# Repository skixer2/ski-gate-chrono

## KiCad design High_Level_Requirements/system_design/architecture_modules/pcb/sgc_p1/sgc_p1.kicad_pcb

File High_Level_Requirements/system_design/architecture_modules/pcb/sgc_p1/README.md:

# SGC P1 — KiCad 8 schematic (generated capture)

**Board:** SGC P1 standalone carrier for u-blox ANNA-B402 — 22 × 55 mm, 4-layer, 0.8 mm, ENIG.
**Source of truth:** `../../sgc_schematic_spec.md` v0.1 (commit 92b352e). Every pin number, pin name
and net in this capture is traceable to that spec (or the datasheet texts it cites). Nothing invented;
everything the spec marks TBD-JP appears as a **text note**, never as a guessed value/net.

## Files

| File | What |
|---|---|
| `sgc_p1.kicad_pro` | KiCad 8 project (minimal) |
| `sgc_p1.kicad_sym` | Project symbol library — 21 symbols (12 ICs/connectors + R/C/L/LED_RGB + 5 power symbols) |
| `sgc_p1.kicad_sch` | Single A3 landscape sheet, KiCad 8 format (version 20231120) |
| `sgc_netlist.py` | **Data**: symbol pin tables + per-component net assignment (edit here first) |
| `gen_symbols.py` | Regenerates `sgc_p1.kicad_sym` from the netlist |
| `gen_schematic.py` | Regenerates `sgc_p1.kicad_sch` + `sgc_p1.kicad_pro` |
| `validate_sgc_p1.py` | Mandatory validation (see below) |

## How to open (KiCad 8.x)

1. Open KiCad 8 → *File → Open Project* → select `sgc_p1.kicad_pro`.
2. Add the symbol library once: *Preferences → Manage Symbol Libraries → Project Libraries → add*
   → `sgc_p1.kicad_sym` (nickname `sgc_p1`). The schematic already embeds every used symbol in its
   `lib_symbols` section, so the sheet displays even before you register the library.
3. Open `sgc_p1.kicad_sch` in Eeschema.

**Regenerate after edits - THREE steps, in this order (order matters):**

```
python3 preserve_layout.py preserve   # 0. capture JP's manual symbol moves (ALWAYS first!)
python3 gen_symbols.py       # 1. regenerate sgc_p1.kicad_sym from SYMBOL_PINS
python3 gen_schematic.py     # 2. write root + child sheets; AUTO re-applies JP's placements
python3 validate_sgc_p1.py   # 3. mandatory validation (all sheets round-trip + union)

PCB stage (since 2026-11-27):

python3 gen_pcb.py          # 4. generate sgc_p1.kicad_pcb: 22x55 board, 79 parts placed per
                            #    PLACEMENT_PLAN v2 (placement_check.P), pads netted from netlist
python3 verify_pcb.py       # 5. semantic gate: re-reads the board file, transforms back to
                            #    plan space, enforces gaps/edges/keepouts on TRUE pad geometry

JP placement preservation (since 2026-11-27): JP moves symbols in KiCad and saves;
'preserve' harvests his positions into layout_positions.json (committed), and
gen_schematic.py translates each part + its labels/stubs/props accordingly.
Translation moves are fully preserved. Symbol ROTATION is not preserved yet
(warned at generation; validator catches label/pin mismatch).
```

**Structure (N1 7-page split, JP GO 2026-11-04):** "sgc_p1.kicad_sch" is a hierarchy-only
root (Arduino ABX00050 style) with six child sheets from "SHEETS" in "sgc_netlist.py":
sch_power (charger/gauge/battery) - sch_mcu (ANNA-B402 + Y1 + SWD) - sch_sensors (BHI260AP
cluster + RGB) - sch_storage (dual MX25R flash) - sch_boost_led (v2 DNP reserve) -
sch_connectors (USB-C/battery/piezo). Every ref sits on exactly ONE sheet (generator
asserts coverage); all connectivity is global labels + power symbols, so sheets bridge by
name with no hierarchical pins. Child-sheet uuids are deterministic (uuid5) so repeated
regeneration keeps the .kicad_pro sheet map stable.

Gotchas learned the hard way:
- kiutils is a hard dependency and does NOT survive a container restart:
  run "pip install --break-system-packages kiutils" (PEP-668 managed Python).
- A crash inside kiutils to_file() can TRUNCATE the target file before writing - if a
  generation run fails, expect zero-byte/partial outputs and re-run after fixing.
- The retired 2-sheet era lives in git history (split_led_sheet.py, led_reserve.kicad_sch);
  the text-surgery approach was dropped for data-driven multi-sheet generation.

Add `--break-system-packages` only because this is a PEP-668 managed Python.
(requires `pip install kiutils`). Edit `sgc_netlist.py`, not the generated files.

## Layout of the sheet (grouped by subsystem)

- **Top-left:** USB-C (J1), CC Rd resistors, VBUS bulk, BQ25120A charger + its R/C network.
- **Bottom-left:** MAX17048 gauge, JST-3 battery connector, SWD header (J3).
- **Center:** ANNA-B402 (U1, all 56 pins incl. 4/7/8 GND from Table 4) + antenna keepout note.
- **Right:** BHI260AP (U8, all 44 pads), BMP390L (U9), flash U7/U2, IS31FL3194 (U5) + RGB LED (D1).
- **Bottom-middle:** LDC1612 (U6, DNP v2) + peripheral/v2 notes (boost, SK6812, Y1, TPs, DNP list).

Connectivity style: **global labels on short stubs** for every pin (61 named nets) + **power symbols**
(`#PWR01…`, per zone anchors) on the power nets GND / +1V8 / VBAT / V_PMID / VBUS_USB. No sprawling wires.
Note boxes carry all OD callouts, the antenna keepout (SIM App. B), I²C address map and the peripheral/v2 notes.

## Refdes scheme (per task; spec's Nicla numbering preserved where it matters)

U1 ANNA-B402 · U2 MX25R1635F (BHI FW flash, OD-5) · U3 BQ25120A · U4 MAX17048 · U5 IS31FL3194 ·
U6 LDC1612 (DNP) · U7 MX25R6435F · U8 BHI260AP · U9 BMP390L · J1 USB4085 · J2 JST-3 battery ·
J3 SWD 2×5 · D1 SMLP34RGB2W3 · C1–C16 · R1–R10 · L1. (Nicla-schematic numbering had IS31=U8 — remapped here.)

## What is decided vs TBD-JP (OD summary — all also on the sheet as notes)

**Decided & captured:** charger resistor network (1.82k/1k/4.99k/100k), all decoupling per spec §6,
I²C pull-ups 100 k→+1V8 (i2c0), BHI RESETN→P0.13 (C3/OD-7), BQ CD→P0.08 + 100k PU V_PMID (C2/OD-8),
boost EN→P0.17 (C1), gauge ALRT→P0.21 + 10k PU, XL2→GND, ANT_INT↔ANT bridge, ANT_PCB→GND pattern
(corner placement), U2 QSPI nets, LDC ADDR→GND (0x2A) + INTB→BUTTON (OD-11), SWD pinout.

**TBD-JP — represented as notes only (never guessed):**
- **OD-4** battery connector PN + cell confirm; NTC R_HI/R_LO values (need Renata R25/B).
- **OD-5** U2 added to BOM (drawn populated, Nicla parity).
- **OD-6** BME688 populate-vs-DNP (not drawn; note at U8 — rides BHI M1 with BMM150).
- **OD-9 / OD-9b** +5 V level translator part (TXB0102-class); SK6812 strip stays on P0.19 pending R2 bench.
- **OD-10** Y1 SIT1532AI fit (default fit; XL1 net `32K_XL1`, note only).
- **OD-12** MAX17048 VIH vs 1.8 V pull-ups — verify before freezing pull-up rail.
- **OD-13** USB ESD part (PESD5V0U2UT vs TPD4E05U06) — note at J1, not drawn.
- **OD-16** module order code + corner placement confirm.
- **OD-17** IS31 SDB net on Nicla + its decap value (SDB→V_PMID drawn per default).
- BHI **HOSTBOOT(3)/VREG(6)** NC v1 (not in spec §6 — decoupling TBD-JP vs Bosch ds); M1/M2/M3 cluster
  wiring = **copy ABX00050 at capture** (BMM150/BME688 not drawn); BMP390 INT(7) NC (DNC per ds);
  RGB LED common polarity verify (IS31 OUTs are current sinks; spec text says anodes to OUTs).
- Boost (MT3608 + SK6812 ×5), RV-3028-C7, U2/strip passives: **note boxes only** — capture at layout. *(BZ1 beeper removed from the project 2026-11-22 — F14, no footprint.)*
- TP set per OD-3: note only.

## Footprint guidance

Pre-assigned (standard lib): R/C/L 0402 (caps ≥4.7 µF 0603), U7/U2 `Package_SO:SOIC-8_5.23x5.23mm_P1.27mm`.
Left EMPTY → **custom footprints needed:** U1 ANNA-B402 LGA pattern (u-blox land pattern), U3 BQ25120A
YFP-25 DSBGA, U4 MAX17048 TDFN-8, U8 BHI260AP LGA-44, U5 IS31 WLCSP-8, U9 BMP390 LGA-10, U6 LDC WSON-12,
J1 USB4085 mid-mount, J2 JST-3 (PN per OD-4), J3 (2×5 1.27 mm Cortex-Debug style **or Tag-Connect
TC2050** per OD-2), D1 SMLP34RGB2W3. These can be generated later from the datasheet land patterns.

## Console pads + pogo jig (rev A)

`TP_TX` (P0.20) / `TP_RX` (P0.09) / `TP_GND` are bare 1.0 mm ENIG test points for a
bidirectional UART console. They carry no part, no BOM line, no assembly step and no
current, so they stay on production units at zero cost (JP 2026-11-22).

**Registration:** `MH1`/`MH2` are 1.6 mm NPTH holes and `FID1`/`FID2` are optical
fiducials, so a printed jig can be located. The hole pair is **deliberately asymmetric**
(17 mm / 13 mm either side of the pad centroid): a symmetric pair lets the jig drop on
180 degrees rotated, which would land jig-TX on TP_GND and jig-GND on TP_TX - two outputs
driving each other with no current limiting.

**PROVISIONAL:** there is no PCB layout yet, so the coordinates in `sgc_netlist.py` are
schematic-sheet millimetres, not board positions. Treat MH/FID and the 10 mm pad pitch as
intent, not fab data. Final pad/hole datum must be set in layout against the printed jig
(JP designs and prints the jig). Pad pitch is shown at 10 mm for schematic legibility and
can be tightened once wire routing is regenerated for the new positions.

**Do NOT use magnetic-base probe fixtures** (e.g. PCBite) on this board: the BMM150 is
populated and its magnetometer feeds the BHY260AP rotation-vector fusion, so nearby
permanent magnets corrupt heading and calibration.

## ERC / validation status

- **Syntax:** both KiCad files parse clean with kiutils (round-trip write + re-read) — see below.
- **Netlist:** independently re-extracted from sheet geometry (wire endpoints + labels + power symbols)
  and compared pin-by-pin against `sgc_netlist.py`: **271/271 pin connections correct, 0 shorts,
  0 floating labels, 0 mid-span taps** (the hidden-short class KiCad auto-junctions).
- **Census:** 40 components (9 U + 3 J + 16 C + 10 R + 1 L + 1 D) vs spec net lists; pin counts:
  B402 56, BQ 25, MAX17048 9 (incl. EP), BHI 44, BMP390 10, LDC 12, IS31 8, MX25R 8+8, USB4085 20, JST 3, SWD 10.
- **NOT claimed:** no electrical-correctness/ERC guarantee beyond the above — run KiCad's ERC after JP
  review; expect informational warnings (single-sheet, NC pins on unused pads, v2 reserved nets).

Run validation: `python3 validate_sgc_p1.py` (exit 0 = green).

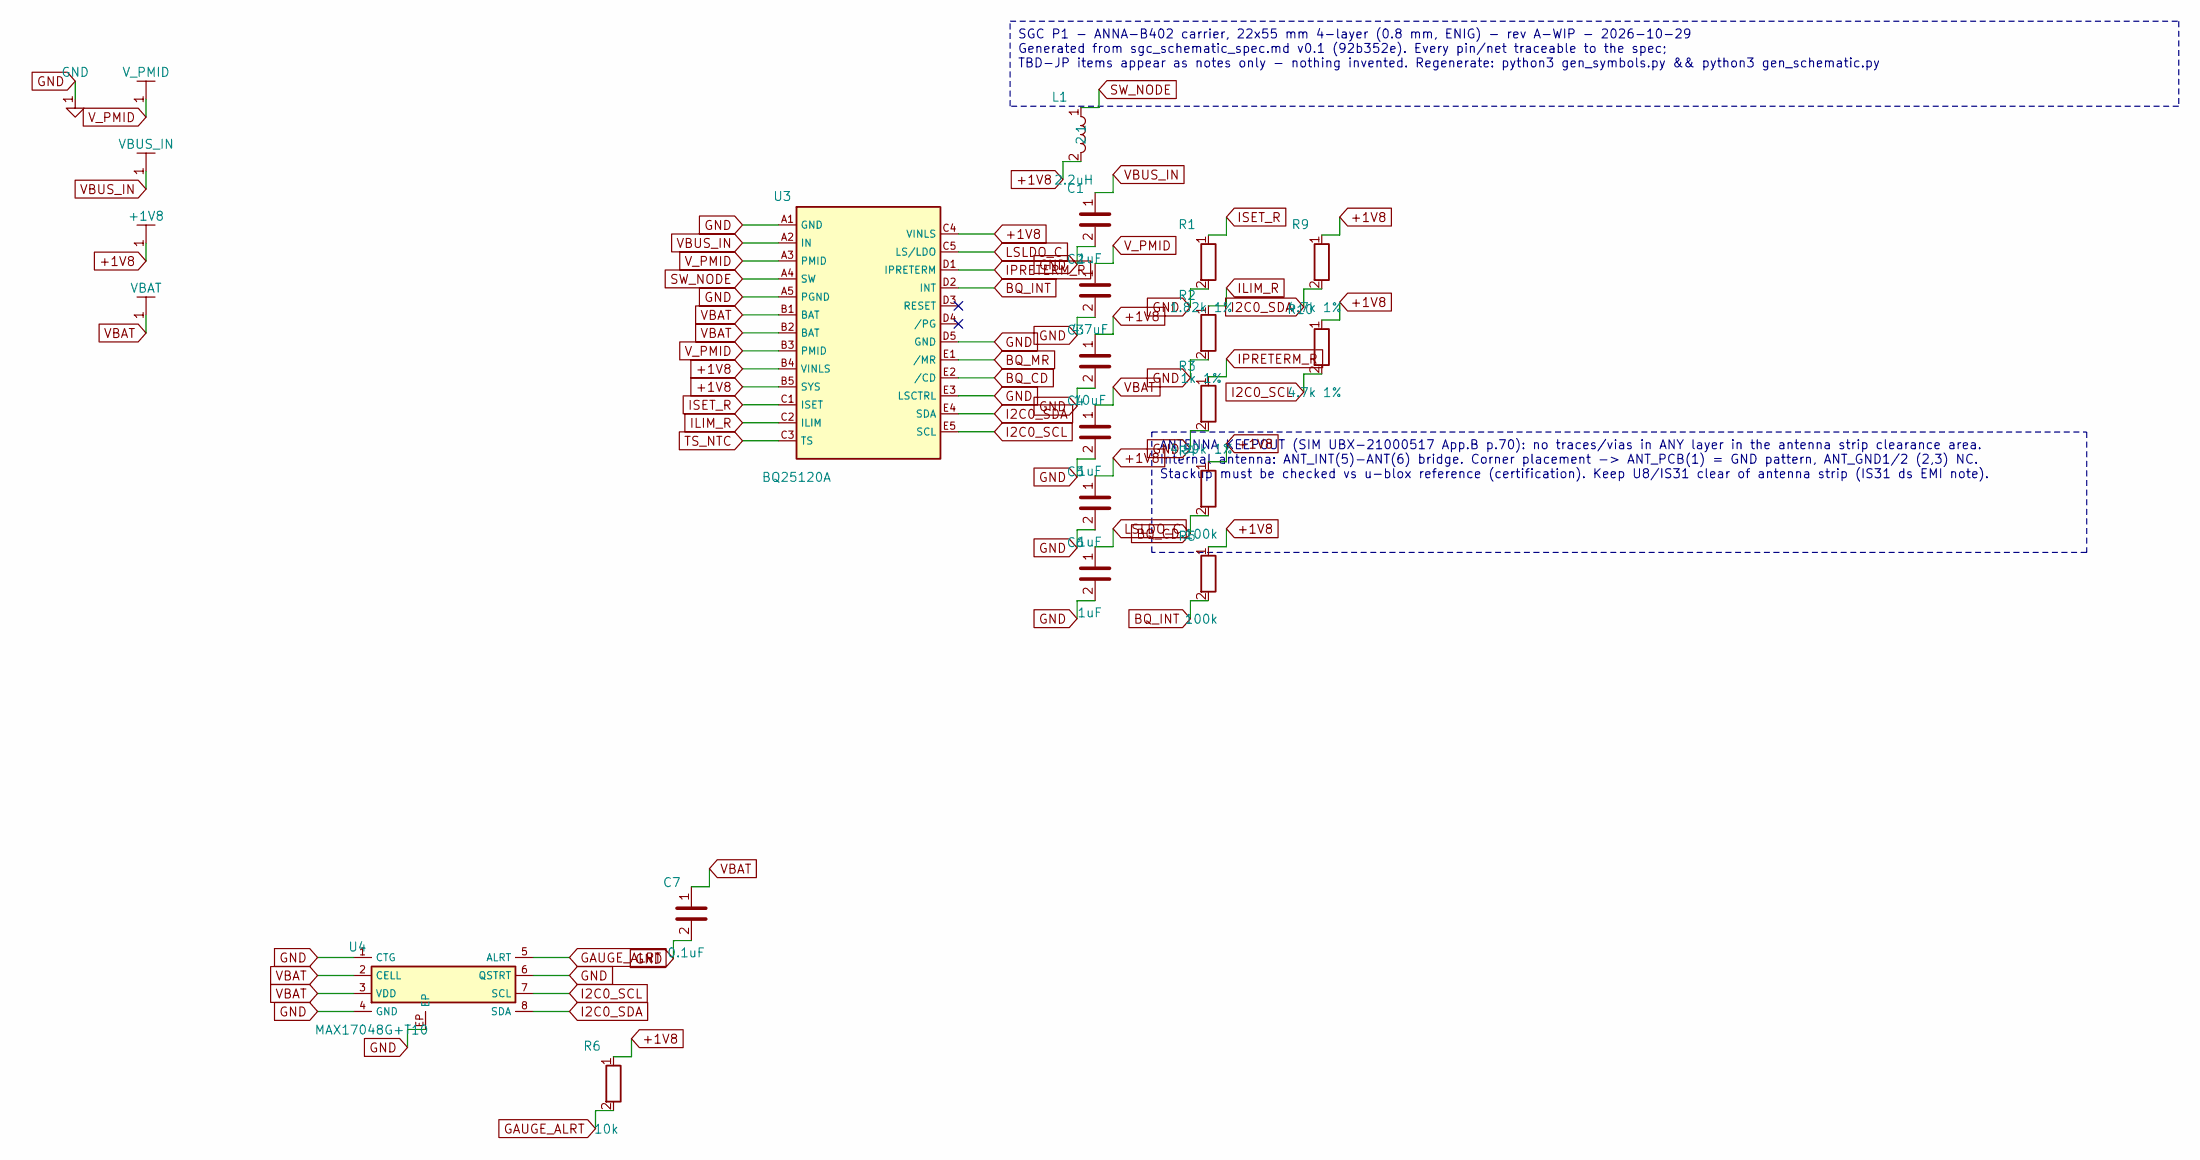
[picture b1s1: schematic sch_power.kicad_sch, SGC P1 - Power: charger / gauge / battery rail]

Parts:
C1, C4, C5, C6: 1uF; C_0402_1005Metric
C2: 4.7uF; C_0603_1608Metric
C3: 10uF; C_0603_1608Metric
C7: 0.1uF; C_0402_1005Metric
L1: 2.2uH; L_0603_1608Metric
R1: 1.82k 1%; R_0402_1005Metric
R2: 1k 1%; R_0402_1005Metric
R3: 4.99k 1%; R_0402_1005Metric
R4, R5: 100k; R_0402_1005Metric
R6: 10k; R_0402_1005Metric
R9, R10: 4.7k 1%; R_0402_1005Metric
U3: BQ25120A; Texas_DSBGA-25_YFP0025_1.6x1.6mm_Layout5x5_P0.4mm
U4: MAX17048G+T10; Maxim_TDFN-8-1EP_2x2mm_P0.5mm_EP0.8x1.38mm_MAX17048

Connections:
+1V8: C3.1, C5.1, L1.2, R4.1, R5.1, R6.1, R9.1, R10.1, U3.B4 (VINLS), U3.B5 (SYS), U3.C4 (VINLS); also elsewhere on the board
BQ_CD: R4.2, U3.E2 (/CD); also elsewhere on the board
BQ_INT: R5.2, U3.D2 (INT)
BQ_MR: U3.E1 (/MR); also elsewhere on the board
GAUGE_ALRT: R6.2, U4.5 (ALRT); also elsewhere on the board
GND: C1.2, C2.2, C3.2, C4.2, C5.2, C6.2, C7.2, R1.2, R2.2, R3.2, U3.A1 (GND), U3.A5 (PGND), U3.D5 (GND), U3.E3 (LSCTRL), U4.1 (CTG), U4.4 (GND), U4.6 (QSTRT), U4.EP; also elsewhere on the board
I2C0_SCL: R10.2, U3.E5 (SCL), U4.7 (SCL); also elsewhere on the board
I2C0_SDA: R9.2, U3.E4 (SDA), U4.8 (SDA); also elsewhere on the board
ILIM_R: R2.1, U3.C2 (ILIM)
IPRETERM_R: R3.1, U3.D1 (IPRETERM)
ISET_R: R1.1, U3.C1 (ISET)
LSLDO_C: C6.1, U3.C5 (LS/LDO)
SW_NODE: L1.1, U3.A4 (SW)
TS_NTC: U3.C3 (TS); also elsewhere on the board
VBAT: C4.1, C7.1, U3.B1 (BAT), U3.B2 (BAT), U4.2 (CELL), U4.3 (VDD); also elsewhere on the board
VBUS_IN: C1.1, U3.A2 (IN); also elsewhere on the board
V_PMID: C2.1, U3.A3 (PMID), U3.B3 (PMID); also elsewhere on the board

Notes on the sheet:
SGC P1 - ANNA-B402 carrier, 22x55 mm 4-layer (0.8 mm, ENIG) - rev A-WIP - 2026-10-29 Generated from sgc_schematic_spec.md v0.1 (92b352e). Every pin/net traceable to the spec; TBD-JP items appear as notes only - nothing invented. Regenerate: python3 gen_symbols.py && python3 gen_schematic.py
ANTENNA KEEPOUT (SIM UBX-21000517 App.B p.70): no traces/vias in ANY layer in the antenna strip clearance area. Internal antenna: ANT_INT(5)-ANT(6) bridge. Corner placement -> ANT_PCB(1) = GND pattern, ANT_GND1/2 (2,3) NC. Stackup must be checked vs u-blox reference (certification). Keep U8/IS31 cl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

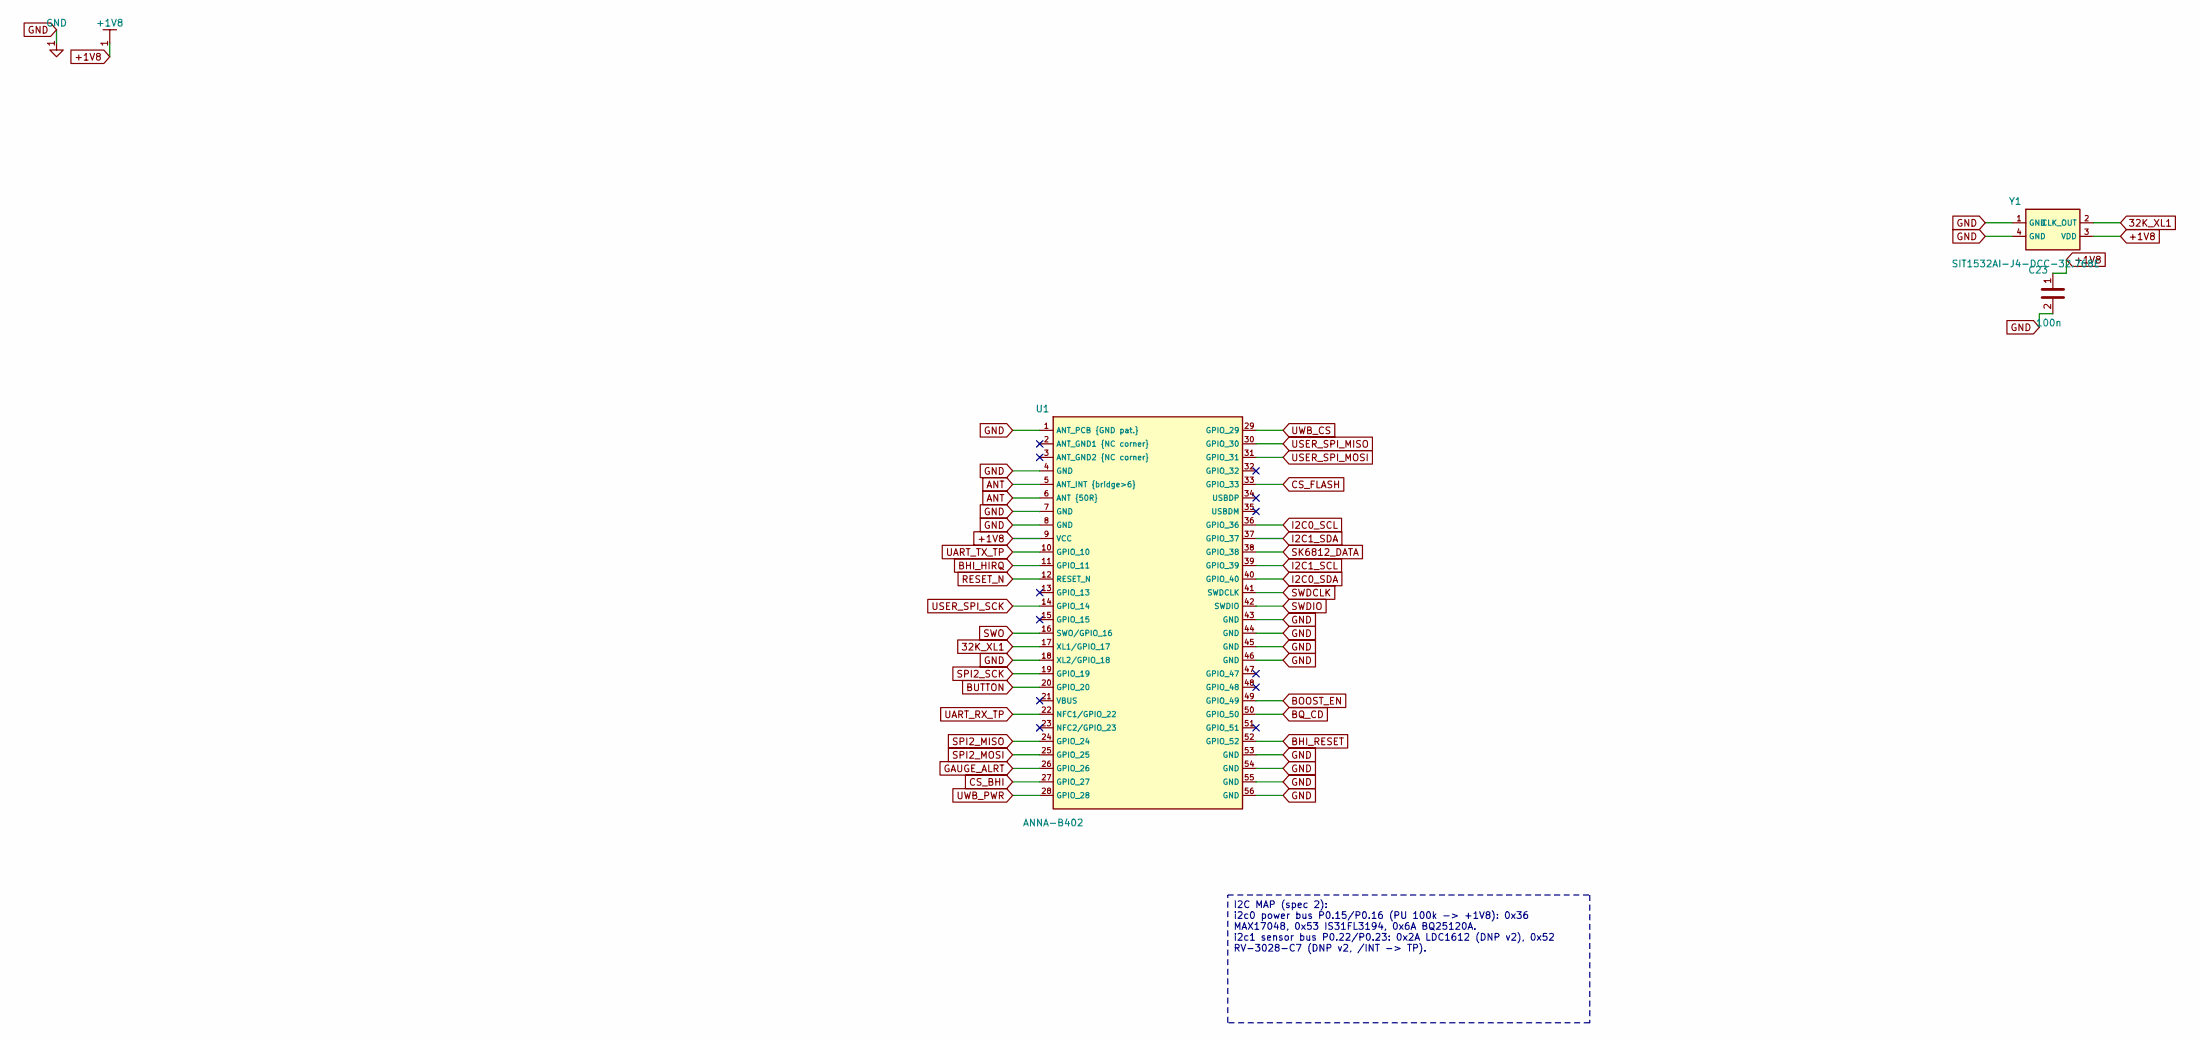
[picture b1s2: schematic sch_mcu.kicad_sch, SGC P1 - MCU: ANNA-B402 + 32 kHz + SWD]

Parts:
C23: 100n; C_0402_1005Metric
U1: ANNA-B402; ANNA-B402_UBL
Y1: SIT1532AI-J4-DCC-32.768E; SIT1532_CSP-4_1p5x0p8mm

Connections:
32K_XL1: U1.17 (XL1/GPIO_17), Y1.2 (CLK_OUT)
+1V8: C23.1, U1.9 (VCC), Y1.3 (VDD); also elsewhere on the board
ANT: U1.5 (ANT_INT {bridge>6}), U1.6 (ANT {50R})
BHI_HIRQ: U1.11 (GPIO_11); also elsewhere on the board
BHI_RESET: U1.52 (GPIO_52); also elsewhere on the board
BOOST_EN: U1.49 (GPIO_49); also elsewhere on the board
BQ_CD: U1.50 (GPIO_50); also elsewhere on the board
BUTTON: U1.20 (GPIO_20); also elsewhere on the board
CS_BHI: U1.27 (GPIO_27); also elsewhere on the board
CS_FLASH: U1.33 (GPIO_33); also elsewhere on the board
GAUGE_ALRT: U1.26 (GPIO_26); also elsewhere on the board
GND: C23.2, U1.1 (ANT_PCB {GND pat.}), U1.4 (GND), U1.7 (GND), U1.8 (GND), U1.18 (XL2/GPIO_18), U1.43 (GND), U1.44 (GND), U1.45 (GND), U1.46 (GND), U1.53 (GND), U1.54 (GND), U1.55 (GND), U1.56 (GND), Y1.1 (GND), Y1.4 (GND); also elsewhere on the board
I2C0_SCL: U1.36 (GPIO_36); also elsewhere on the board
I2C0_SDA: U1.40 (GPIO_40); also elsewhere on the board
I2C1_SCL: U1.39 (GPIO_39); also elsewhere on the board
I2C1_SDA: U1.37 (GPIO_37); also elsewhere on the board
RESET_N: U1.12 (RESET_N); also elsewhere on the board
SK6812_DATA: U1.38 (GPIO_38); also elsewhere on the board
SPI2_MISO: U1.24 (GPIO_24); also elsewhere on the board
SPI2_MOSI: U1.25 (GPIO_25); also elsewhere on the board
SPI2_SCK: U1.19 (GPIO_19); also elsewhere on the board
SWDCLK: U1.41 (SWDCLK); also elsewhere on the board
SWDIO: U1.42 (SWDIO); also elsewhere on the board
SWO: U1.16 (SWO/GPIO_16); also elsewhere on the board
UART_RX_TP: U1.22 (NFC1/GPIO_22); also elsewhere on the board
UART_TX_TP: U1.10 (GPIO_10); also elsewhere on the board
USER_SPI_MISO: U1.30 (GPIO_30)
USER_SPI_MOSI: U1.31 (GPIO_31)
USER_SPI_SCK: U1.14 (GPIO_14)
UWB_CS: U1.29 (GPIO_29)
UWB_PWR: U1.28 (GPIO_28)

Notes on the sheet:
I2C MAP (spec 2): i2c0 power bus P0.15/P0.16 (PU 100k -> +1V8): 0x36 MAX17048, 0x53 IS31FL3194, 0x6A BQ25120A. i2c1 sensor bus P0.22/P0.23: 0x2A LDC1612 (DNP v2), 0x52 RV-3028-C7 (DNP v2, /INT -> TP).

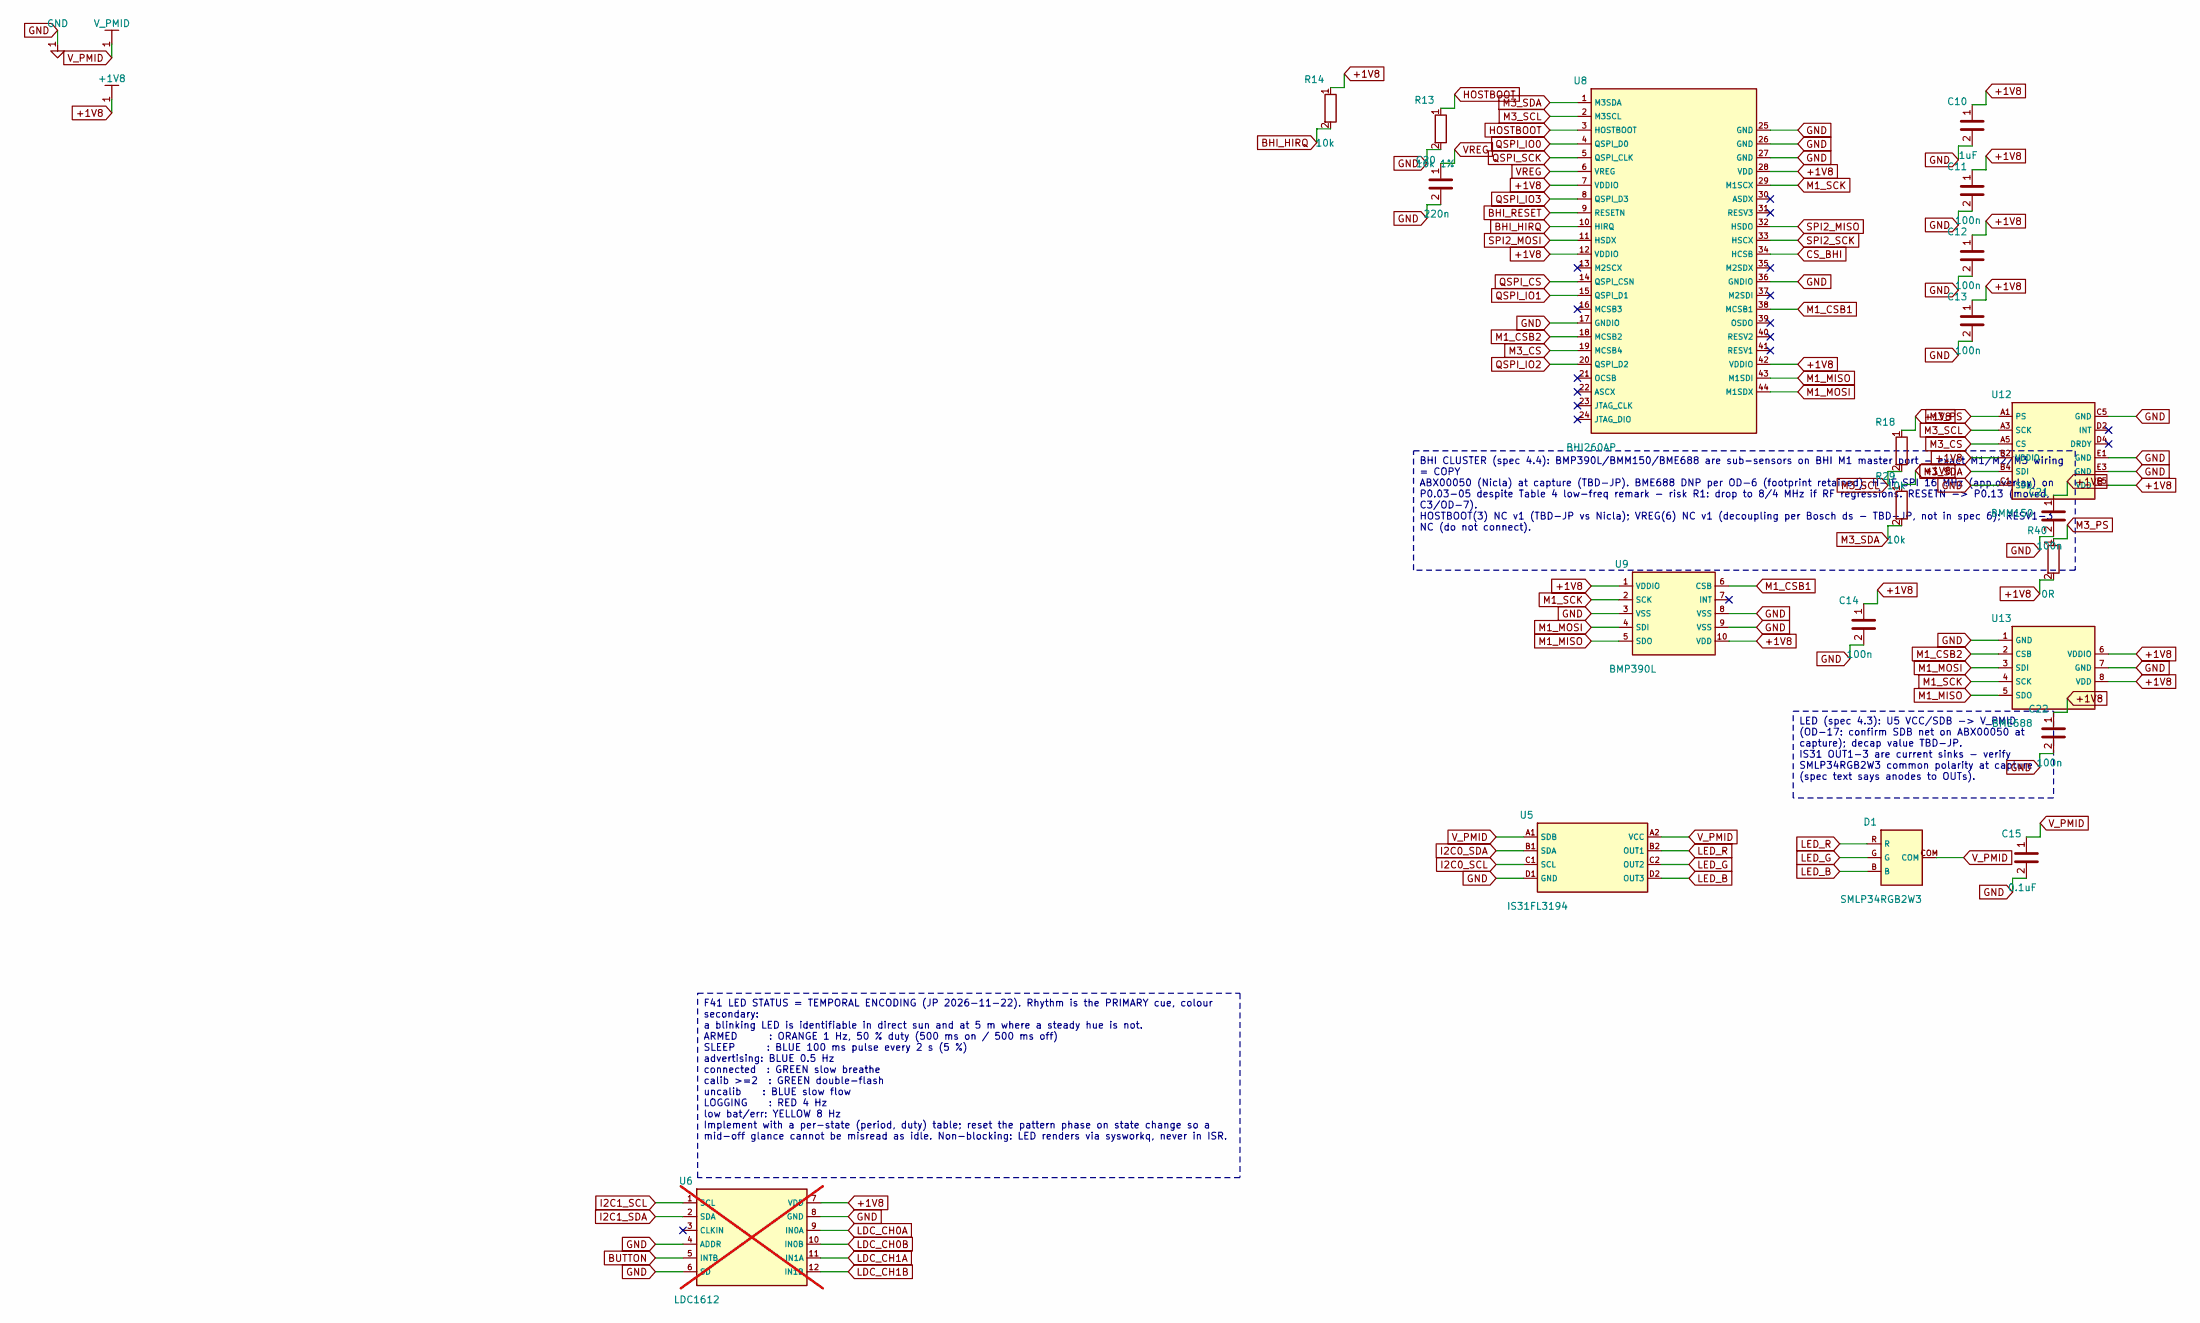
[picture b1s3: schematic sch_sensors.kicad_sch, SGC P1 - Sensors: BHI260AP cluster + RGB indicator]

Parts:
C10: 1uF; C_0402_1005Metric
C11, C12, C13, C14, C21, C22: 100n; C_0402_1005Metric
C15: 0.1uF; C_0402_1005Metric
C20: 220n; C_0402_1005Metric
D1: SMLP34RGB2W3; Rohm_PicoLEDF_1010_1x1mm_SMLP34RGB2W3
R13: 10k 1%; R_0402_1005Metric
R14, R18, R29: 10k; R_0402_1005Metric
R40: 0R; R_0402_1005Metric
U5: IS31FL3194; Lumissil_WLCSP-8_0.99x1.59mm_P0.4mm_IS31FL3194
U6: LDC1612; WSON-12-1EP_4x4mm_P0.5mm_EP2.6x3mm; not fitted
U8: BHI260AP; Bosch_BHI260AP_LGA-44_P0.4mm_2ring
U9: BMP390L; Bosch_BMP390_LGA-10_2x2mm
U12: BMM150; Bosch_BMM150_WLCSP-12_1.56x1.56mm
U13: BME688; Bosch_BME688_LGA-8_3x3mm_P0.8mm

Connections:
+1V8: C10.1, C11.1, C12.1, C13.1, C14.1, C21.1, C22.1, R14.1, R18.1, R29.1, R40.2, U6.7 (VDD), U8.7 (VDDIO), U8.12 (VDDIO), U8.28 (VDD), U8.42 (VDDIO), U9.1 (VDDIO), U9.10 (VDD), U12.B2 (VDDIO), U12.E5 (VDD), U13.6 (VDDIO), U13.8 (VDD); also elsewhere on the board
BHI_HIRQ: R14.2, U8.10 (HIRQ); also elsewhere on the board
BHI_RESET: U8.9 (RESETN); also elsewhere on the board
BUTTON: U6.5 (INTB); also elsewhere on the board
CS_BHI: U8.34 (HCSB); also elsewhere on the board
GND: C10.2, C11.2, C12.2, C13.2, C14.2, C15.2, C20.2, C21.2, C22.2, R13.2, U5.D1 (GND), U6.4 (ADDR), U6.6 (SD), U6.8 (GND), U8.17 (GNDIO), U8.25 (GND), U8.26 (GND), U8.27 (GND), U8.36 (GNDIO), U9.3 (VSS), U9.8 (VSS), U9.9 (VSS), U12.C1 (SDO), U12.C5 (GND), U12.E1 (GND), U12.E3 (GND), U13.1 (GND), U13.7 (GND); also elsewhere on the board
HOSTBOOT: R13.1, U8.3 (HOSTBOOT)
I2C0_SCL: U5.C1 (SCL); also elsewhere on the board
I2C0_SDA: U5.B1 (SDA); also elsewhere on the board
I2C1_SCL: U6.1 (SCL); also elsewhere on the board
I2C1_SDA: U6.2 (SDA); also elsewhere on the board
LDC_CH0A: U6.9 (IN0A)
LDC_CH0B: U6.10 (IN0B)
LDC_CH1A: U6.11 (IN1A)
LDC_CH1B: U6.12 (IN1B)
LED_B: D1.3, D1.B, U5.D2 (OUT3)
LED_G: D1.4, D1.G, U5.C2 (OUT2)
LED_R: D1.2, D1.R, U5.B2 (OUT1)
M1_CSB1: U8.38 (MCSB1), U9.6 (CSB)
M1_CSB2: U8.18 (MCSB2), U13.2 (CSB)
M1_MISO: U8.43 (M1SDI), U9.5 (SDO), U13.5 (SDO)
M1_MOSI: U8.44 (M1SDX), U9.4 (SDI), U13.3 (SDI)
M1_SCK: U8.29 (M1SCX), U9.2 (SCK), U13.4 (SCK)
M3_CS: U8.19 (MCSB4), U12.A5 (CS)
M3_PS: R40.1, U12.A1 (PS)
M3_SCL: R18.2, U8.2 (M3SCL), U12.A3 (SCK)
M3_SDA: R29.2, U8.1 (M3SDA), U12.B4 (SDI)
QSPI_CS: U8.14 (QSPI_CSN); also elsewhere on the board
QSPI_IO0: U8.4 (QSPI_D0); also elsewhere on the board
QSPI_IO1: U8.15 (QSPI_D1); also elsewhere on the board
QSPI_IO2: U8.20 (QSPI_D2); also elsewhere on the board
QSPI_IO3: U8.8 (QSPI_D3); also elsewhere on the board
QSPI_SCK: U8.5 (QSPI_CLK); also elsewhere on the board
SPI2_MISO: U8.32 (HSDO); also elsewhere on the board
SPI2_MOSI: U8.11 (HSDX); also elsewhere on the board
SPI2_SCK: U8.33 (HSCX); also elsewhere on the board
VREG: C20.1, U8.6 (VREG)
V_PMID: C15.1, D1.1, D1.COM, U5.A1 (SDB), U5.A2 (VCC); also elsewhere on the board

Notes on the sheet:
BHI CLUSTER (spec 4.4): BMP390L/BMM150/BME688 are sub-sensors on BHI M1 master port - exact M1/M2/M3 wiring = COPY ABX00050 (Nicla) at capture (TBD-JP). BME688 DNP per OD-6 (footprint retained). H-IF SPI 16 MHz (app.overlay) on P0.03-05 despite Table 4 low-freq remark - risk R1: drop to 8/4 MHz if 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
LED (spec 4.3): U5 VCC/SDB -> V_PMID (OD-17: confirm SDB net on ABX00050 at capture); decap value TBD-JP. IS31 OUT1-3 are current sinks - verify SMLP34RGB2W3 common polarity at capture (spec text says anodes to OUTs).
F41 LED STATUS = TEMPORAL ENCODING (JP 2026-11-22). Rhythm is the PRIMARY cue, colour secondary: a blinking LED is identifiable in direct sun and at 5 m where a steady hue is not. ARMED : ORANGE 1 Hz, 50 % duty (500 ms on / 500 ms off) SLEEP : BLUE 100 ms pulse every 2 s (5 %) advertising: BLUE 0.5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

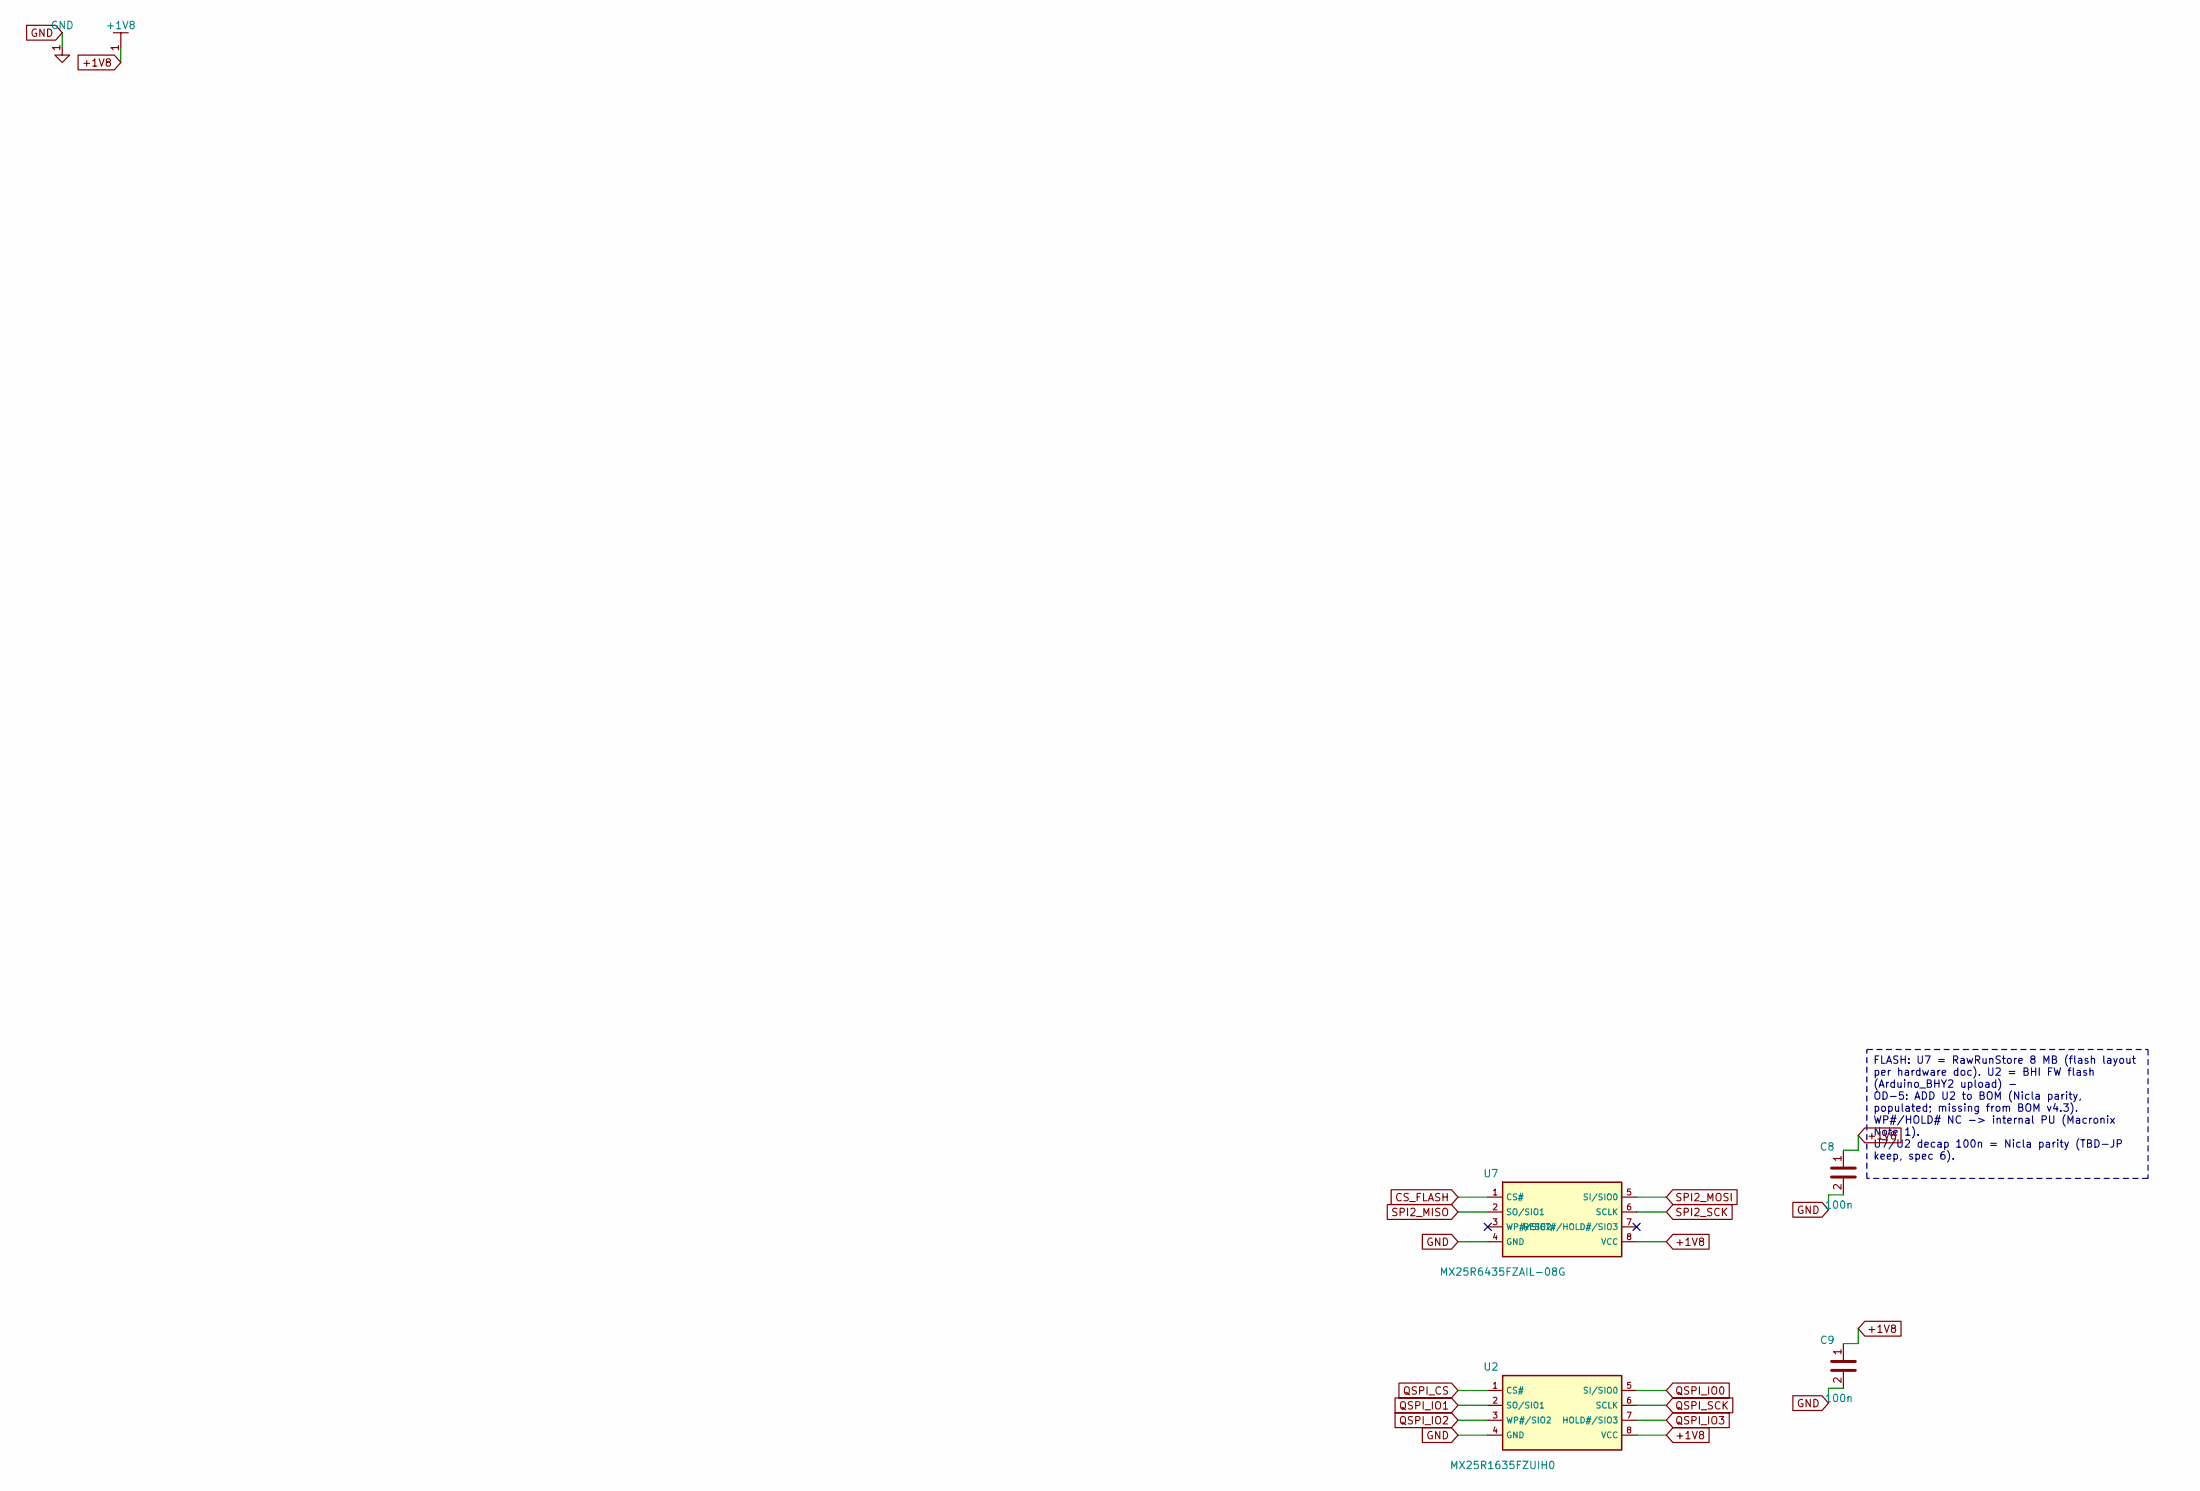
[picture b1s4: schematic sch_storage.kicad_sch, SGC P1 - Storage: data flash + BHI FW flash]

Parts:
C8, C9: 100n; C_0402_1005Metric
U2: MX25R1635FZUIH0; SOIC-8_5.23x5.23mm_P1.27mm
U7: MX25R6435FZAIL-08G; SOIC-8_5.23x5.23mm_P1.27mm

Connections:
+1V8: C8.1, C9.1, U2.8 (VCC), U7.8 (VCC); also elsewhere on the board
CS_FLASH: U7.1 (CS#); also elsewhere on the board
GND: C8.2, C9.2, U2.4 (GND), U7.4 (GND); also elsewhere on the board
QSPI_CS: U2.1 (CS#); also elsewhere on the board
QSPI_IO0: U2.5 (SI/SIO0); also elsewhere on the board
QSPI_IO1: U2.2 (SO/SIO1); also elsewhere on the board
QSPI_IO2: U2.3 (WP#/SIO2); also elsewhere on the board
QSPI_IO3: U2.7 (HOLD#/SIO3); also elsewhere on the board
QSPI_SCK: U2.6 (SCLK); also elsewhere on the board
SPI2_MISO: U7.2 (SO/SIO1); also elsewhere on the board
SPI2_MOSI: U7.5 (SI/SIO0); also elsewhere on the board
SPI2_SCK: U7.6 (SCLK); also elsewhere on the board

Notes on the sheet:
FLASH: U7 = RawRunStore 8 MB (flash layout per hardware doc). U2 = BHI FW flash (Arduino_BHY2 upload) - OD-5: ADD U2 to BOM (Nicla parity, populated; missing from BOM v4.3). WP#/HOLD# NC -> internal PU (Macronix Note 1). U7/U2 decap 100n = Nicla parity (TBD-JP keep, spec 6).

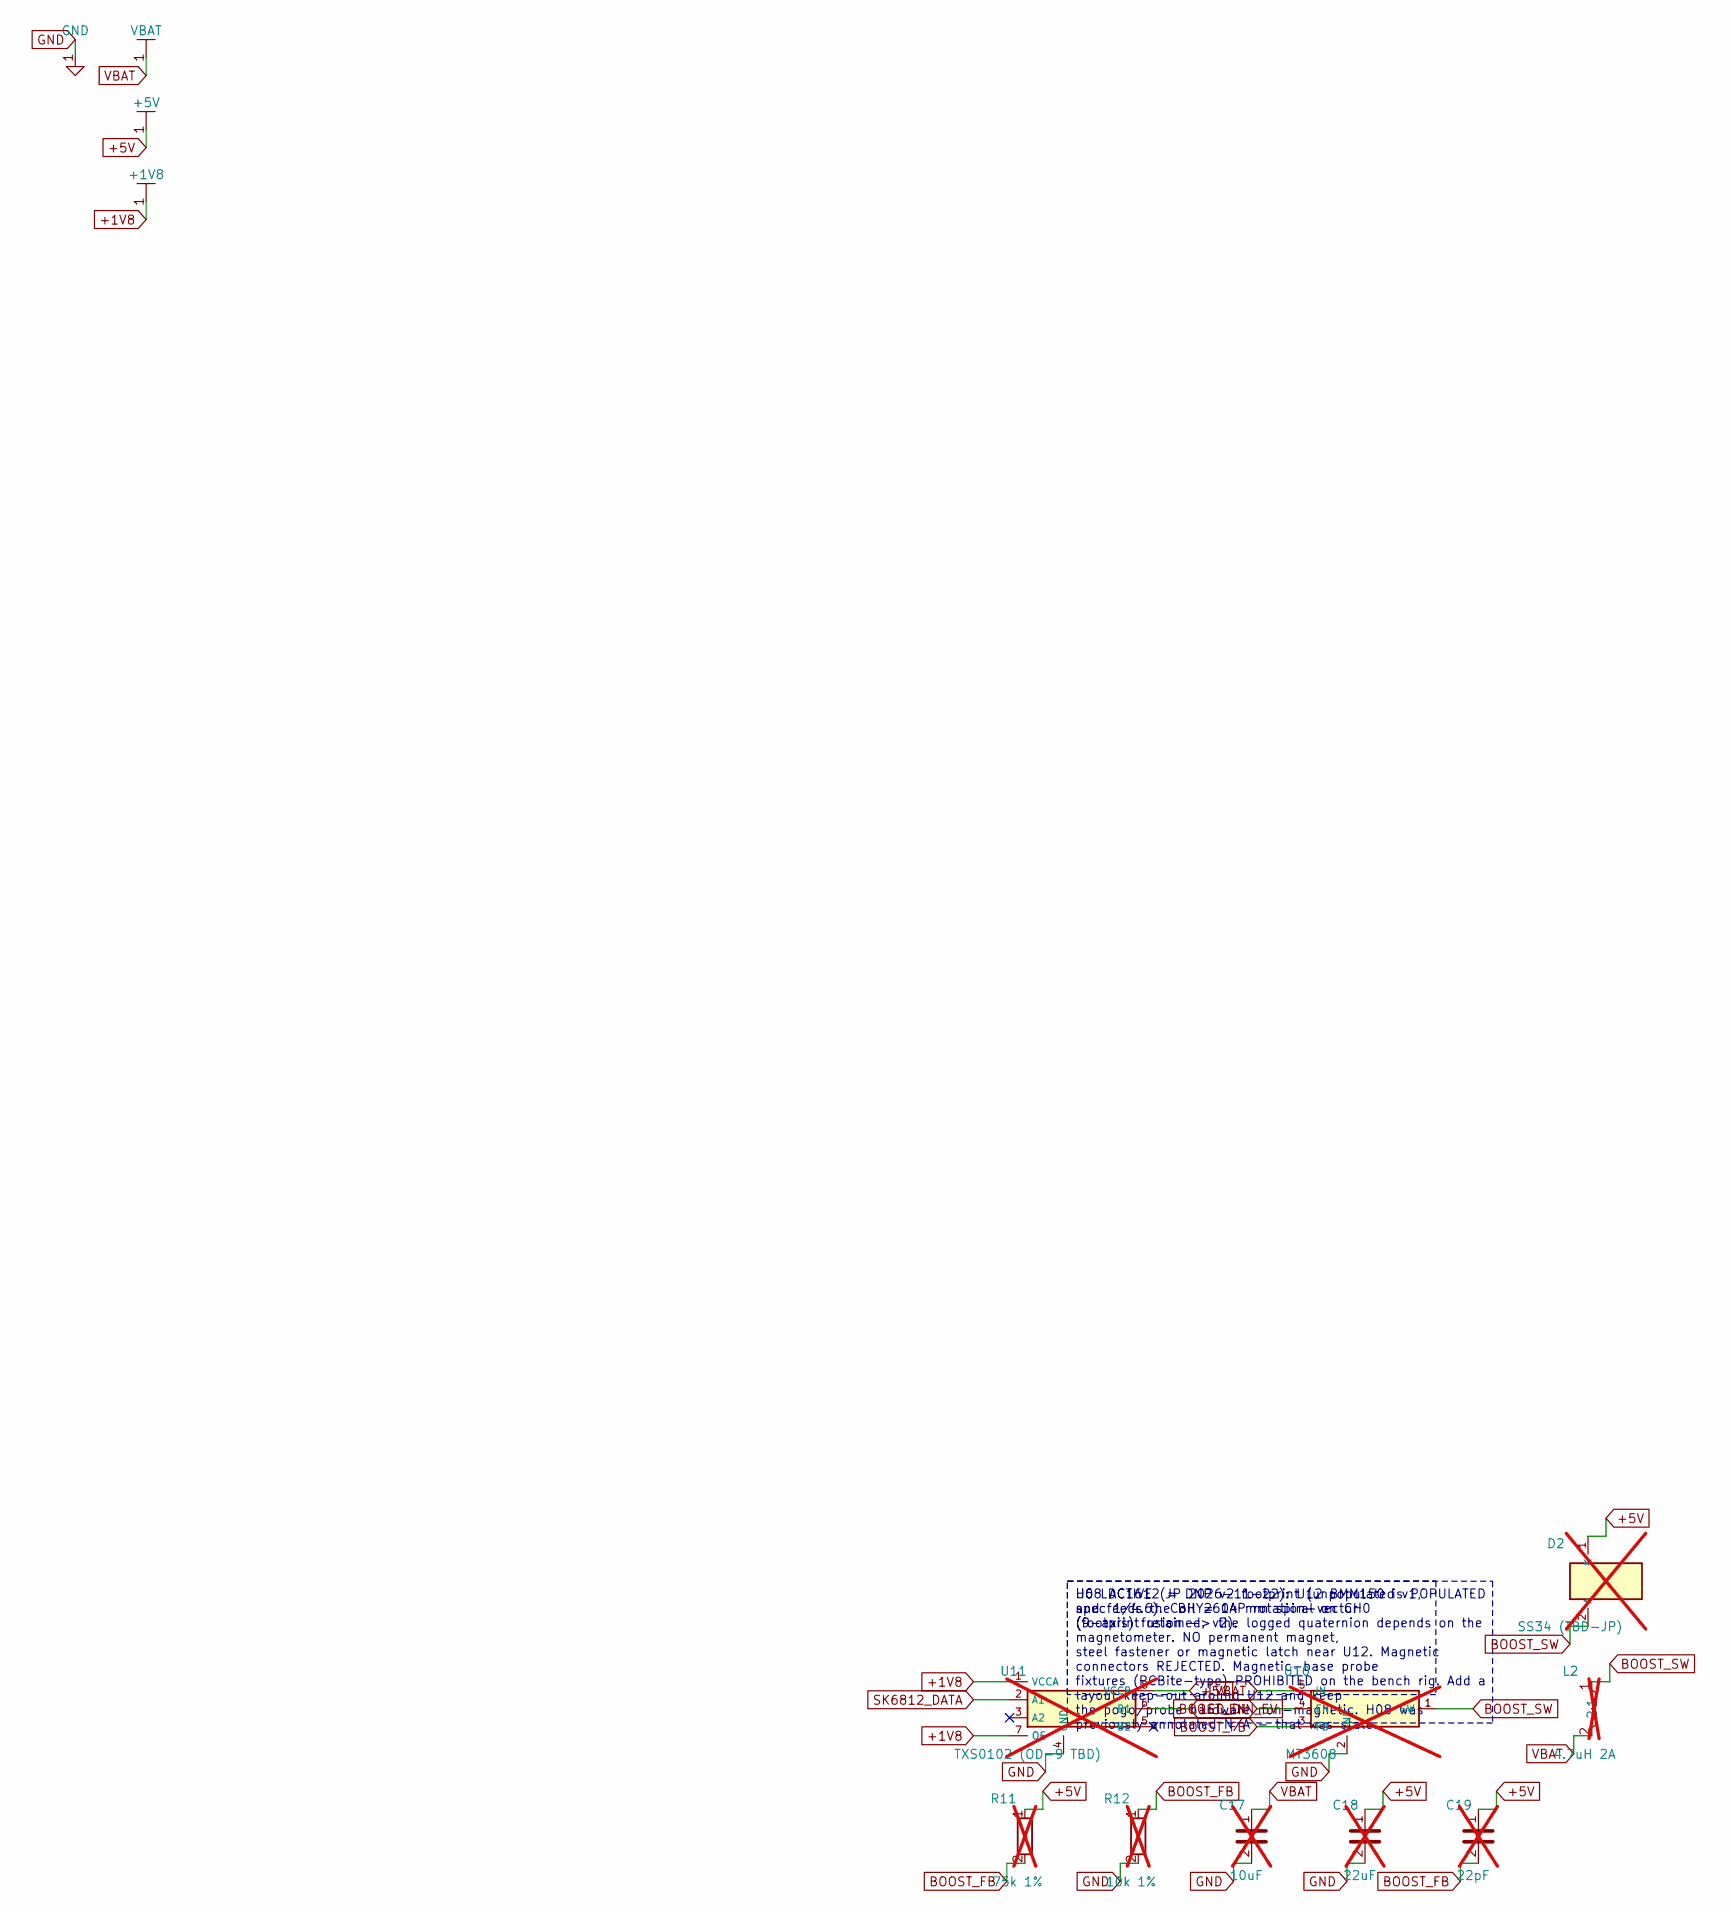
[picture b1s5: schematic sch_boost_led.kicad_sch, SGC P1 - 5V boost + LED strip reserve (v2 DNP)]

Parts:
C17: 10uF; C_0603_1608Metric; not fitted
C18: 22uF; C_0805_2012Metric; not fitted
C19: 22pF; C_0402_1005Metric; not fitted
D2: SS34 (TBD-JP); D_SMA; not fitted
L2: 4.7uH 2A; L_0805_2012Metric; not fitted
R11: 75k 1%; R_0402_1005Metric; not fitted
R12: 10k 1%; R_0402_1005Metric; not fitted
U10: MT3608; SOT-23-6; not fitted
U11: TXS0102 (OD-9 TBD); VSSOP-8_2.3x2mm_P0.5mm; not fitted

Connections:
+1V8: U11.1 (VCCA), U11.7 (OE); also elsewhere on the board
+5V: C18.1, C19.1, D2.1 (K), R11.1, U11.8 (VCCB); also elsewhere on the board
BOOST_EN: U10.4 (EN); also elsewhere on the board
BOOST_FB: C19.2, R11.2, R12.1, U10.3 (FB)
BOOST_SW: D2.2 (A), L2.1, U10.1 (SW)
GND: C17.2, C18.2, R12.2, U10.2 (GND), U11.4 (GND); also elsewhere on the board
LED_DIN_5V: U11.6 (B1); also elsewhere on the board
SK6812_DATA: U11.2 (A1); also elsewhere on the board
VBAT: C17.1, L2.2, U10.5 (IN); also elsewhere on the board

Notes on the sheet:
U6 LDC1612 = DNP v2 footprint (unpopulated v1, spec 1/4.6). Coil = 14 mm spiral on CH0 (footprint retained, v2).
H08 ACTIVE (JP 2026-11-22): U12 BMM150 is POPULATED and feeds the BHY260AP rotation-vector (9-axis) fusion -> the logged quaternion depends on the magnetometer. NO permanent magnet, steel fastener or magnetic latch near U12. Magnetic connectors REJECTED. Magnetic-base probe fixtures (PCBite-type) P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
